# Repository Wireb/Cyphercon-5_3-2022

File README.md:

# Cyphercon 5.3 2022 
This repo is a collection of files related to the Cyphercon 5.3 badge and support hardware. 
Peacock board files and data pulled out to make the lifetime badges a bit harder to forge. 

## KiCad
This is a KiCad 5.x project. 

## MplabX
This is a mplabX 5.35 project. All programming / debug was done with a PicKit4.

## FreeCAD
These are FreeCAD 0.19 

## Inkscape
Version 1.0.1 used

## Documentation

- Cyphercon 2020.xlsx - Master document used for badge development. BOMs, communication, game mech, flash layout, animation documentation
- FreeCAD/Start button-2022  Cad files related to the conference start button
- FreeCAD/tymkrs_Cyphercon_2022 Cad files related to the badge and vending machine 
   - bottle_button_support.FCStd - support structure for IR button used in the snake oil button 
   - button_case.FCStd - support structure for IR button used in the bee and bird seed bags
   - coyote_final.FCStd - screen alignment tool
   - coyote_stencil.FCStd - flocking stencil and blocks
   - flamingo_final.FCStd - screen alignment tool
   - flamingo_flock_blocks.FCStd - alignment blocks for badge on stencil machine 
   - flamingo_pgm_fixture.FCStd - programing fixture for flamingo badges
   - flamingo_stencil_2_tone_a.FCStd - flocking stencil
   - flamingo_stencil_V2.FCStd - flocking stencil
   - llama_final.FCStd - screen alignment tool
   - llama_stencil.FCStd - flocking stencil and blocks
   - Outhouse_socket.FCStd - socket for holding badge in outhouse
   - parrot_final.FCStd - screen alignment tool
   - parrot_stencil.FCStd - flocking stencil and blocks
   - peacock_final.FCStd - screen alignment tool
   - port_a_potty.FCStd - port-a-potty IR button housing 
   - Starfish.FCStd - starfish stencil for back of all the badges
   - Vendo_bracket.FCStd - support bracket for replacement processor board in the vending machine
   - Vendo_socket.FCStd - socket for badge on front of the vending machine 
   - wash_holders.FCStd - holder for running PCBs though flux remover in the ultrasonic cleaner
- inkscape - Intermediate files used to build up the stencils from the silk screen layers
- kicad 
   - tymkrs_Cyphercon_2020_Coyote - Coyote badge files
   - tymkrs_Cyphercon_2020_flamingo - Flamingo badge files
   - tymkrs_Cyphercon_2020_IRbutton - IR button files 
   - tymkrs_Cyphercon_2020_IRhack - IR hack and start button board (note start button was highly modified and mostly just used as a PIC chip holder.)
   - tymkrs_Cyphercon_2020_Llama - Llama badge files
   - tymkrs_Cyphercon_2020_Parrot - Parrot badge files 
   - tymkrs_vendo - Vendo processor replacement board (note "vendo.???" files are my schematics from reverse engineering the vending machine board) 
- mplab
    - Tymkrs_Cyphercon2020_IRblaster - Firmware for con start button
    - Tymkrs_Cyphercon2020_IRhack - Firmware for IRhack board 
    - Tymkrs_Cyphercon_2020_badge - Firmware for badges (one build supports all. Function defined by ID range) 
    - Tymkrs_Cyphercon_2020_IRbutton - Firmware for IR buttons and outhouses (Note there is a #ifdef to set outhouse vs IR button mode) 
- perl
   - Animation_build_list - flamingo.txt - build list to go with build_animations.pl script to generate animation_flamingo.bin
   - Animation_build_list_CPL.txt - build list to go with build_animations.pl script to generate animation_CPL.bin
   - Animation_build_list_peacock.txt - build list to go with animation_peacock.pl script to generate animation_flamingo.bin
   - animation_CPL.bin - output animation data file that should be written to the SPI eeprom on the badge for coyote, parrot, and llama
   - animation_flamingo.bin - output animation data file that should be written to the SPI eeprom on the badge
   - animation_peacock.bin - output animation data file that should be written to the SPI eeprom on the badge
   - build_animations.pl - this script takes in the animation frames in PNG format per the animation_build_list and generates the binary files to be written to the - eeprom
   - CPL_eyes - file folder of png files for coyote, parrot, and llama
   - cyphercon2020-pgm.pl - programing script for the PIC generate random key for crypto and takes user input for badge ID (badge type is determined by ID range. See documentation)
   - cyphercon2022.db - database dump from the vending machine 
   - Cyphercon_2020_test.pl - test utility to be use with a IR hack to gest the various badge communication functions
   - F_eyes - file folder of png files for flamingos
   - hbdh.png - Happy birthday Hyr0n (was going to be on his birthday in 2020... Happy belated bday Hyr0n) 
   - metroid.png - PNG used in base firmware to test the LCD when the SPI eeprom is not programed
   - P_eyes - file folder of png files for peacocks
   - Tymkrs_Cyphercon_2020_badge.X.production.hex - final released firmware (should be the same as the copy in the mplab directory... I hope) 
   - Tymkrs_Cyphercon_2020_keys.txt - Master list of keys used in the vending machine. Use the last one in the file when duplicates badge IDs are found. 
   - Vending_data.xlsx - Decoded dump in excel with some post processing to get some stats
   - Vendo_decode.pl - used to export the vending machine database to CSV files
   - Vendo_server.pl - Vending machine server script that did all the vending machine functions other that the monitor display
   - Vendo_test.pl - test script for the vending machine controller board

Copyright (c) 2019 - 2022 Peter Shabino

Permission is hereby granted, free of charge, to any person obtaining a copy of this hardware, software, and associated documentation files 
(the "Product"), to deal in the Product without restriction, including without limitation the rights to use, copy, modify, merge, publish, 
distribute, sublicense, and/or sell copies of the Product, and to permit persons to whom the Product is furnished to do so, subject to the 
following conditions:

The above copyright notice and this permission notice shall be included in all copies or substantial portions of the Product.

THE PRODUCT IS PROVIDED "AS IS", WITHOUT WARRANTY OF ANY KIND, EXPRESS OR IMPLIED, INCLUDING BUT NOT LIMITED TO THE WARRANTIES OF 
MERCHANTABILITY, FITNESS FOR A PARTICULAR PURPOSE AND NONINFRINGEMENT. IN NO EVENT SHALL THE AUTHORS OR COPYRIGHT HOLDERS BE LIABLE 
FOR ANY CLAIM, DAMAGES OR OTHER LIABILITY, WHETHER IN AN ACTION OF CONTRACT, TORT OR OTHERWISE, ARISING FROM, OUT OF OR IN CONNECTION 
WITH THE PRODUCT OR THE USE OR OTHER DEALINGS IN THE PRODUCT.

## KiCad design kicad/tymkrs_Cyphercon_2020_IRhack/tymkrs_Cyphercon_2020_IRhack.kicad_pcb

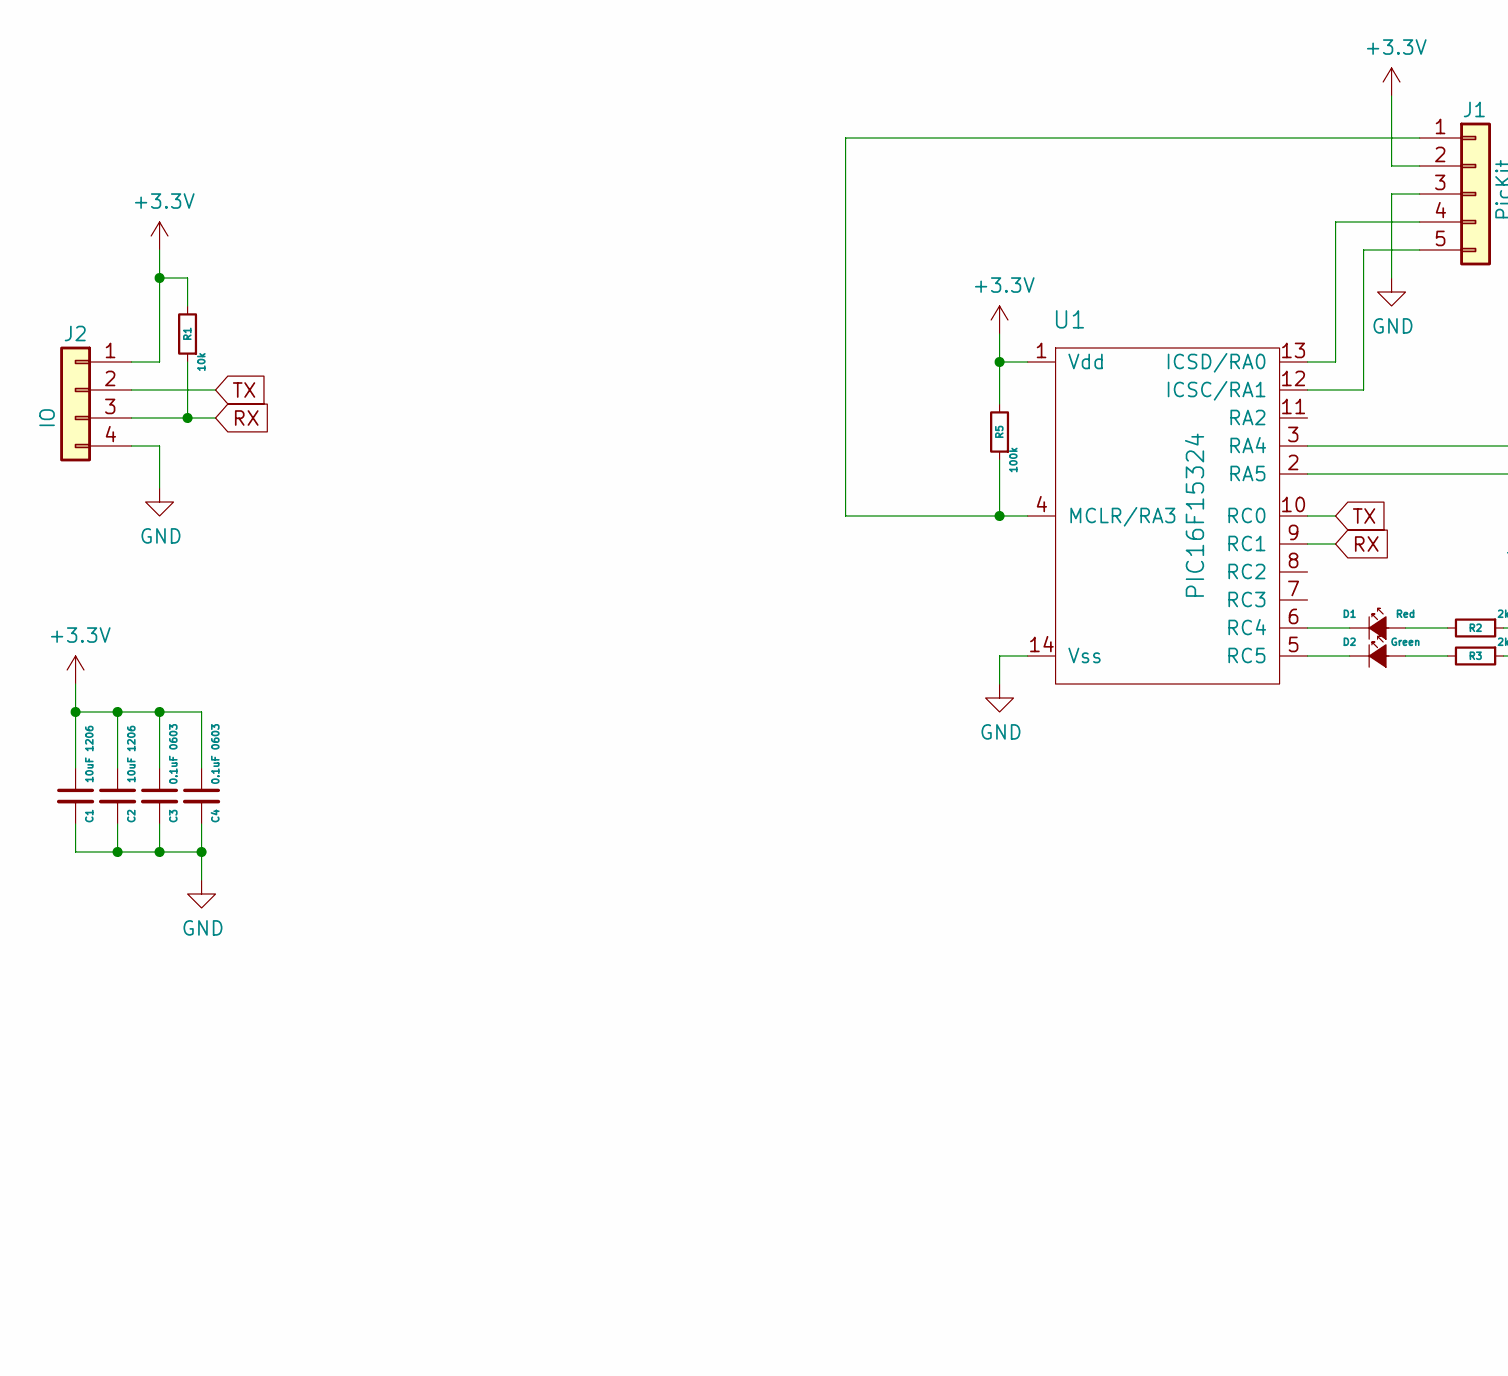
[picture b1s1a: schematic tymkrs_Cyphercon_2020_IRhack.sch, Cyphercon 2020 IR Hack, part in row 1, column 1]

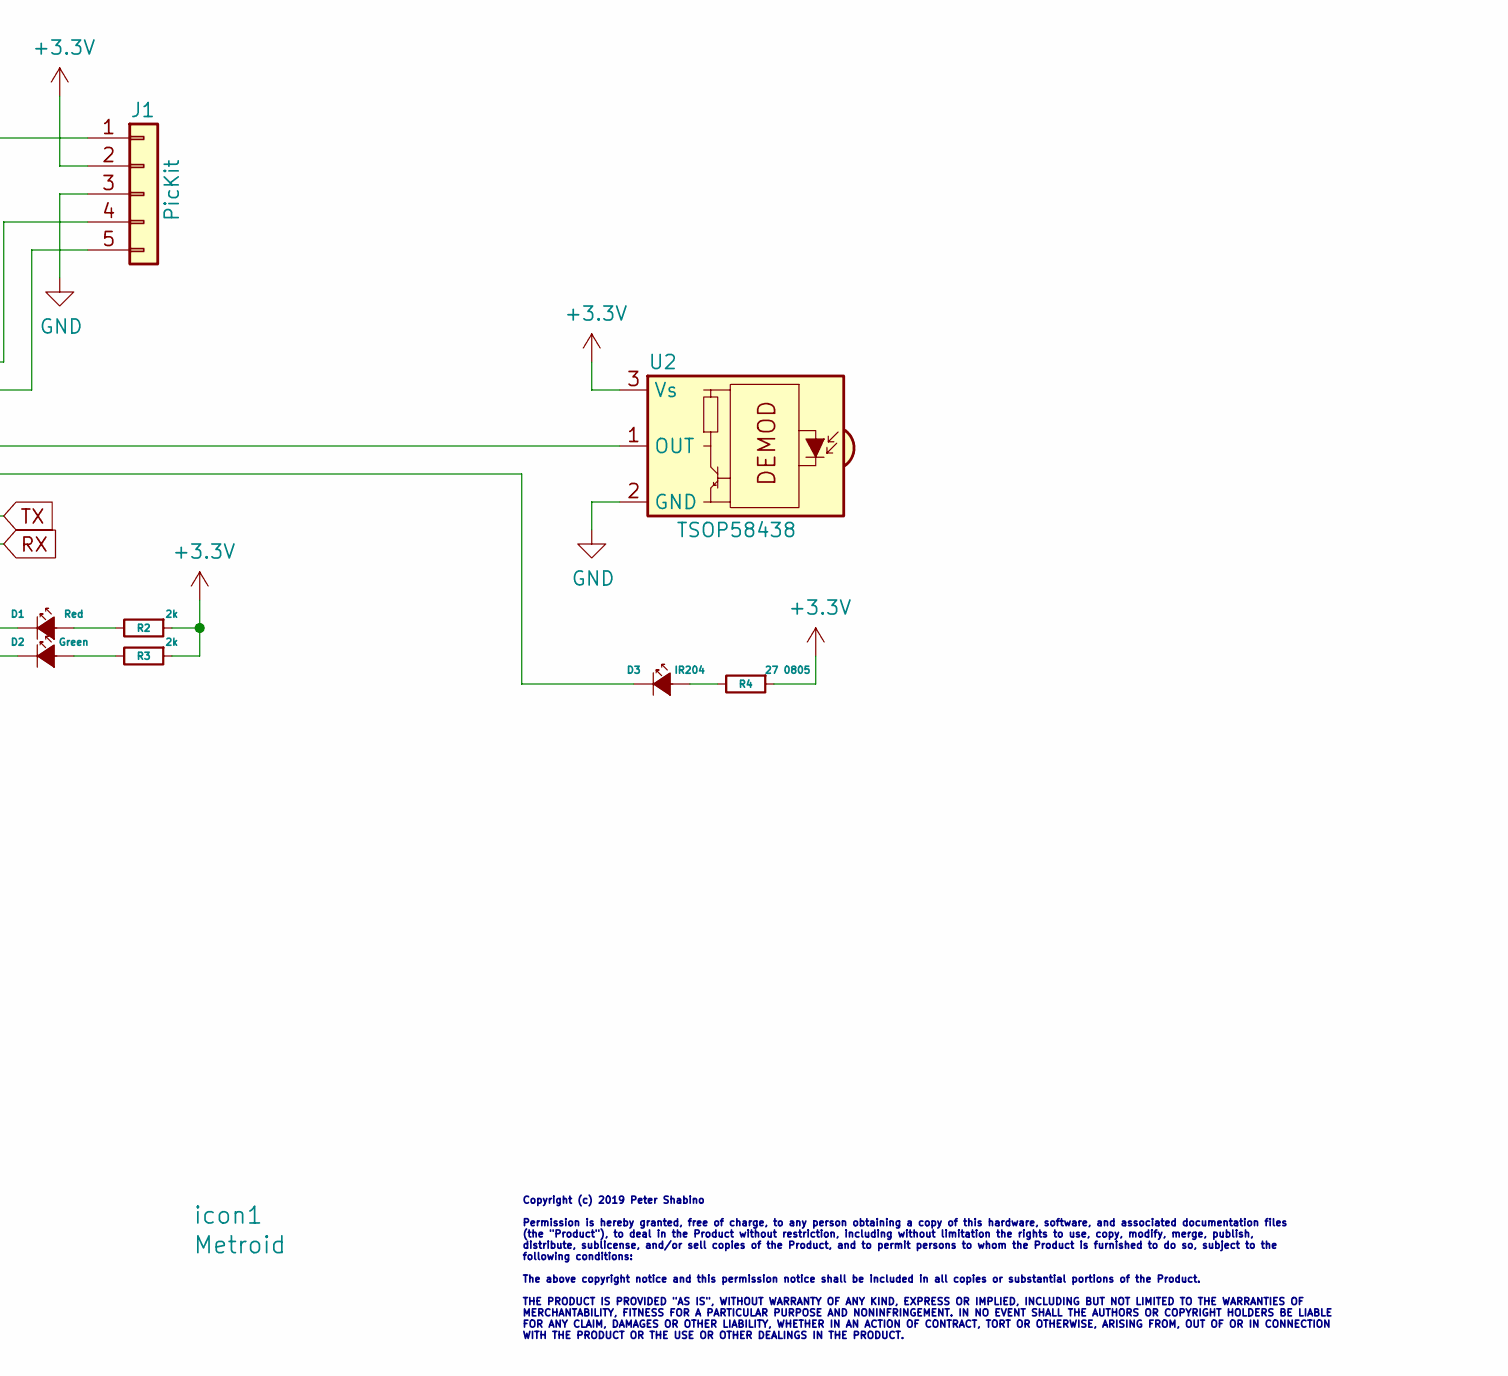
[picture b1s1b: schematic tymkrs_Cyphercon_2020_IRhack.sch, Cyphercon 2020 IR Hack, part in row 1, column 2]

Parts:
C1, C2: 10uF 1206; C_1206_3216Metric
C3, C4: 0.1uF 0603; C_0603_1608Metric
D1: Red; LED_0603_1608Metric
D2: Green; LED_0603_1608Metric
D3: IR204; LED_D3.0mm_Horizontal_O1.27mm_Z2.0mm_Clear
J1: PicKit; PinHeader_1x05_P2.54mm_Vertical
J2: IO; PinHeader_1x04_P2.54mm_Horizontal
R1: 10k; R_0603_1608Metric
R2, R3: 2k; R_0603_1608Metric
R4: 27 0805; R_0603_1608Metric
R5: 100k; R_0603_1608Metric
U1: PIC16F15324; SOIC-14_3.9x8.7mm_P1.27mm
U2: TSOP58438; TSOP48
icon1: Metroid; metroid

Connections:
+3V3: C1.1, C2.1, C3.1, C4.1, J1.2, J2.1, R1.2, R2.1, R3.1, R4.1, R5.2, U1.1 (Vdd), U2.3 (Vs)
GND: C1.2, C2.2, C3.2, C4.2, J1.3, J2.4, U1.14 (Vss), U2.2 (GND)
unnamed: D1.1 (K), U1.6 (RC4)
unnamed: D1.2 (A), R2.2
unnamed: D2.1 (K), U1.5 (RC5)
unnamed: D2.2 (A), R3.2
unnamed: D3.1 (K), U1.2 (RA5)
unnamed: D3.2 (A), R4.2
unnamed: J1.1, R5.1, U1.4 (MCLR/RA3)
unnamed: J1.4, U1.13 (ICSD/RA0)
unnamed: J1.5, U1.12 (ICSC/RA1)
unnamed: U1.3 (RA4), U2.1 (OUT)
RX: J2.3, R1.1, U1.9 (RC1)
TX: J2.2, U1.10 (RC0)

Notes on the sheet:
Copyright (c) 2019 Peter Shabino Permission is hereby granted, free of charge, to any person obtaining a copy of this hardware, software, and associated documentation files (the "Product"), to deal in the Product without restriction, including without limitation the rights to use, copy, modify, mer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

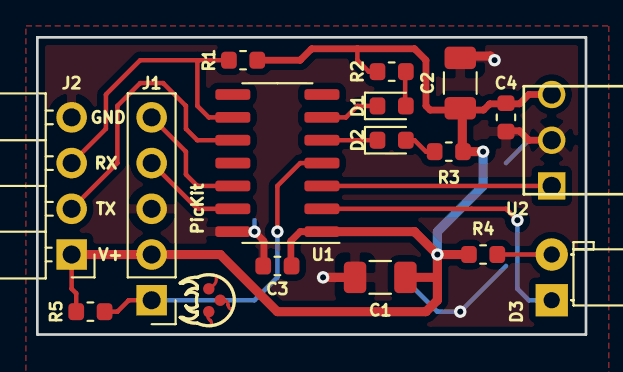
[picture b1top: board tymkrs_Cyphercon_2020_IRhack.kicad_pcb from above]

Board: 2 copper layers, 30.5 x 16.5 mm, 17 parts (0 on the bottom side), 14 nets.

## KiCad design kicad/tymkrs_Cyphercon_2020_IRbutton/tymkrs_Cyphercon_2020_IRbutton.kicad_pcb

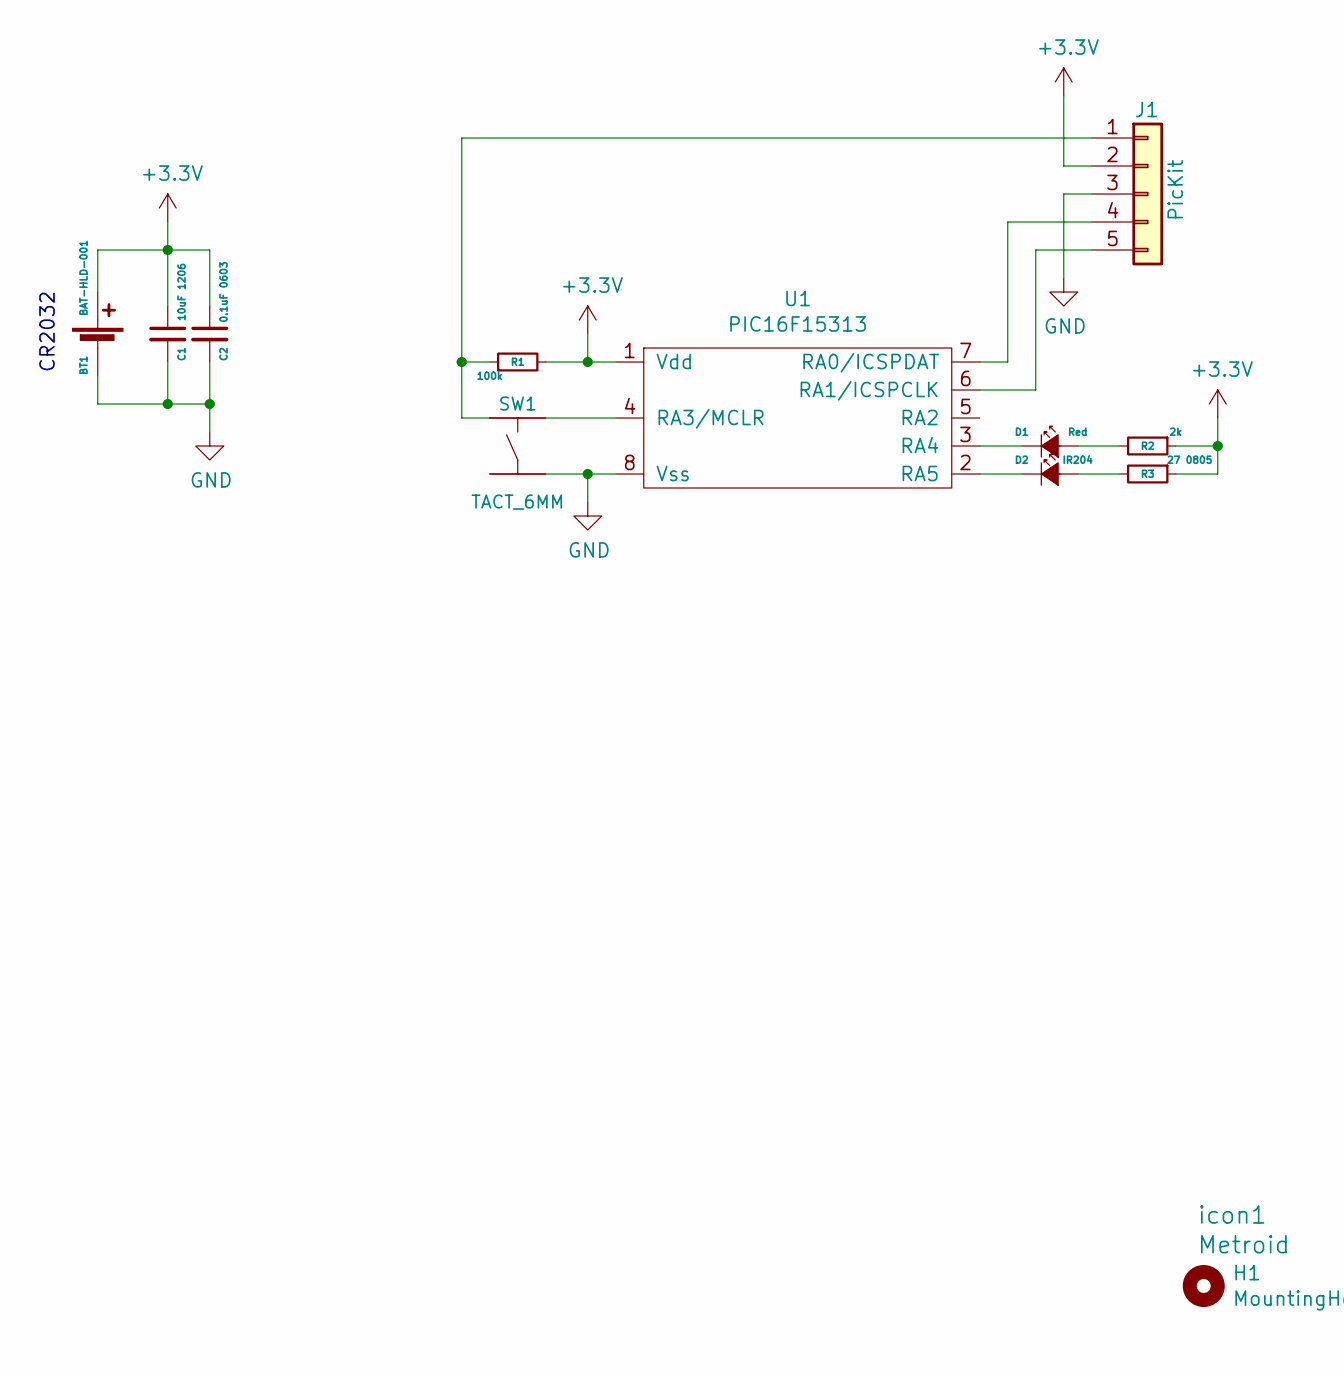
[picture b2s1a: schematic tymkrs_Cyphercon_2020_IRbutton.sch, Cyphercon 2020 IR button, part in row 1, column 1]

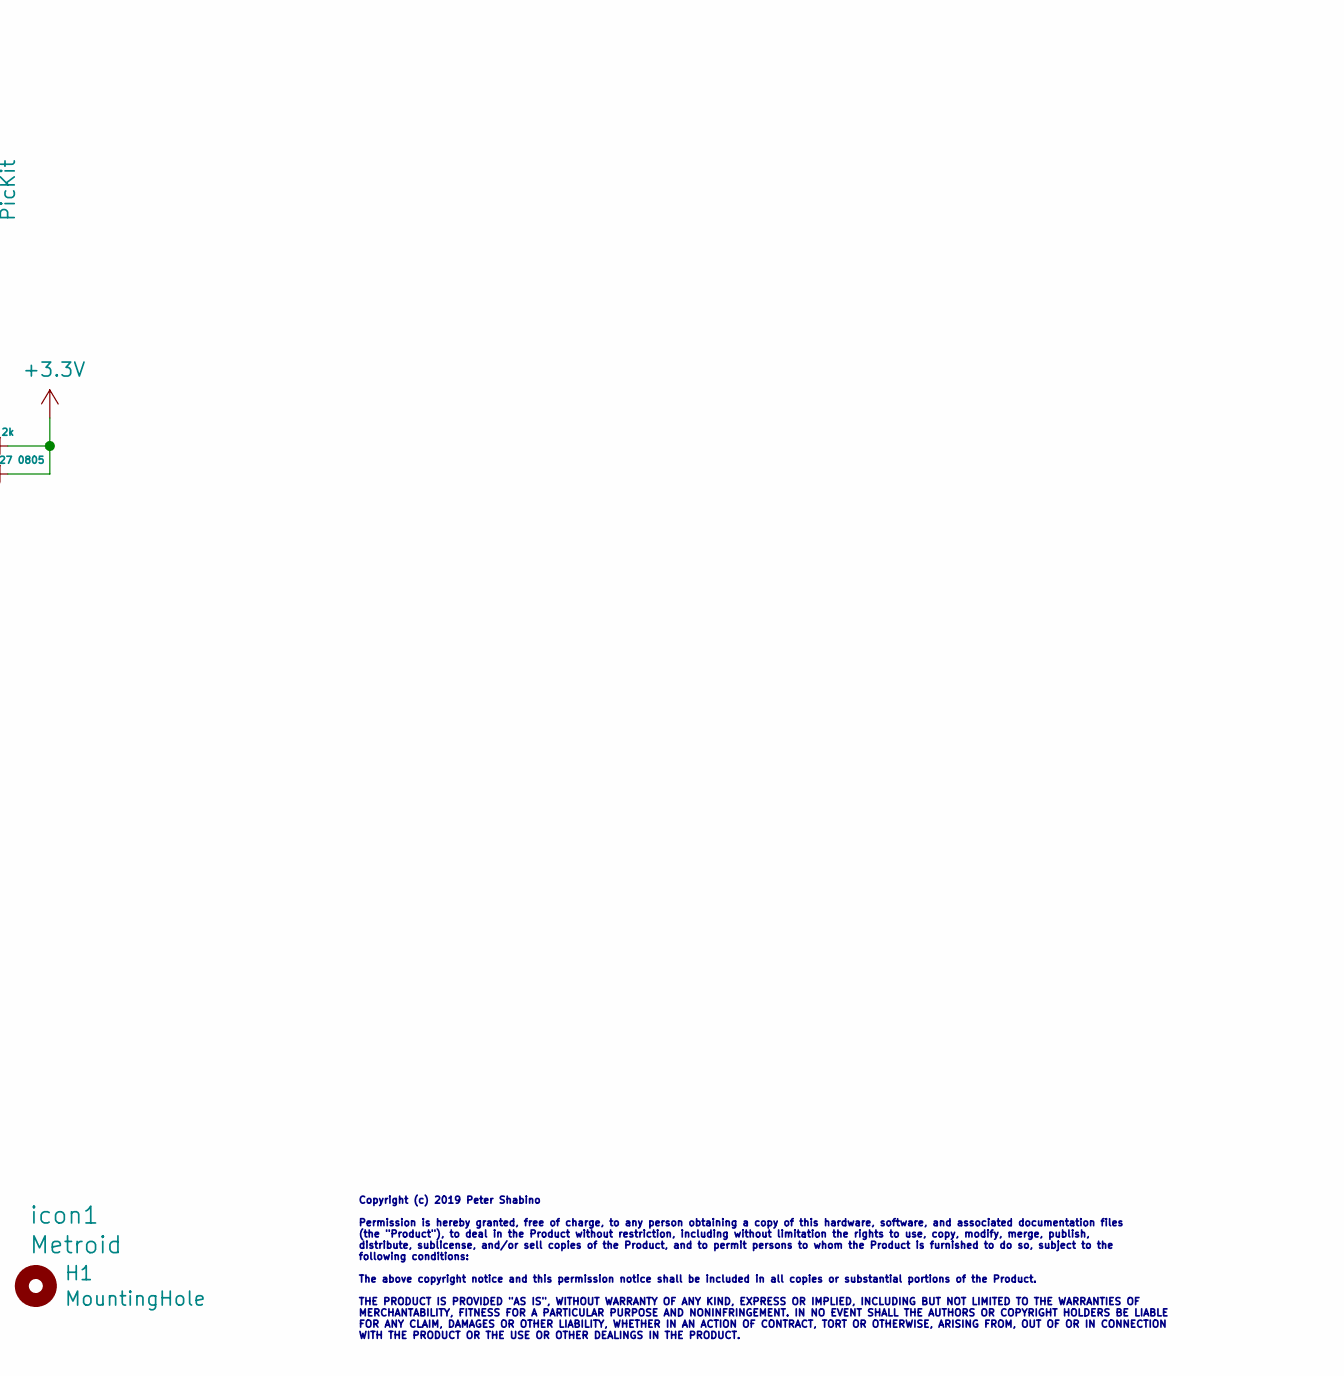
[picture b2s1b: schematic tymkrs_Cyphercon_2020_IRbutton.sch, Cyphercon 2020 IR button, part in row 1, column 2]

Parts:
BT1: BAT-HLD-001
C1: 10uF 1206; C_1206_3216Metric
C2: 0.1uF 0603; C_0603_1608Metric
D1: Red; LED_0603_1608Metric
D2: IR204; LED_D3.0mm_Horizontal_O1.27mm_Z2.0mm_Clear
H1: MountingHole; MountingHole_2.7mm_M2.5
J1: PicKit; PinHeader_1x05_P2.54mm_Vertical
R1: 100k; R_0603_1608Metric
R2: 2k; R_0603_1608Metric
R3: 27 0805; R_0603_1608Metric
SW1: TACT_6MM; PTS645_6mm_tact_sw
U1: PIC16F15313; SOIC-8_3.9x4.9mm_P1.27mm
icon1: Metroid; metroid

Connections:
+3V3: BT1.1 (+), C1.1, C2.1, J1.2, R1.2, R2.1, R3.1, U1.1 (Vdd)
GND: BT1.2 (-), C1.2, C2.2, J1.3, SW1.4, U1.8 (Vss)
unnamed: D1.1 (K), U1.3 (RA4)
unnamed: D1.2 (A), R2.2
unnamed: D2.1 (K), U1.2 (RA5)
unnamed: D2.2 (A), R3.2
unnamed: J1.1, R1.1, SW1.1
unnamed: J1.4, U1.7 (RA0/ICSPDAT)
unnamed: J1.5, U1.6 (RA1/ICSPCLK)
unnamed: SW1.2, U1.4 (RA3/MCLR)

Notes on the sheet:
Copyright (c) 2019 Peter Shabino Permission is hereby granted, free of charge, to any person obtaining a copy of this hardware, software, and associated documentation files (the "Product"), to deal in the Product without restriction, including without limitation the rights to use, copy, modify, mer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
CR2032

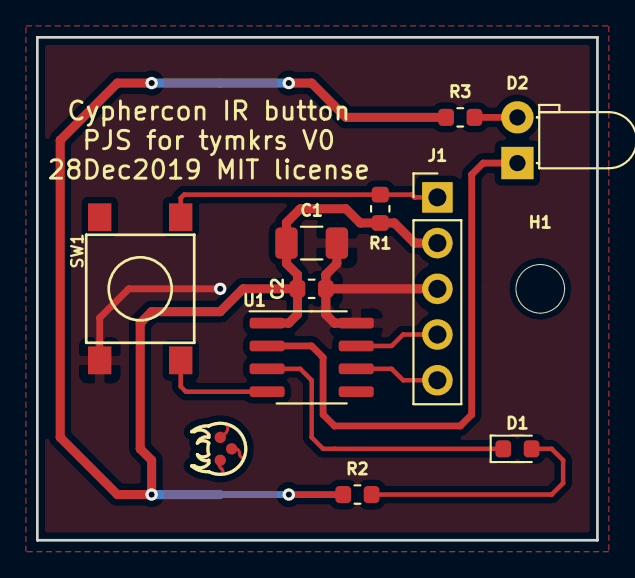
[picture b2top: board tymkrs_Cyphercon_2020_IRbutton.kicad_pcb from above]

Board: 2 copper layers, 31.1 x 27.9 mm, 13 parts (1 on the bottom side), 10 nets.

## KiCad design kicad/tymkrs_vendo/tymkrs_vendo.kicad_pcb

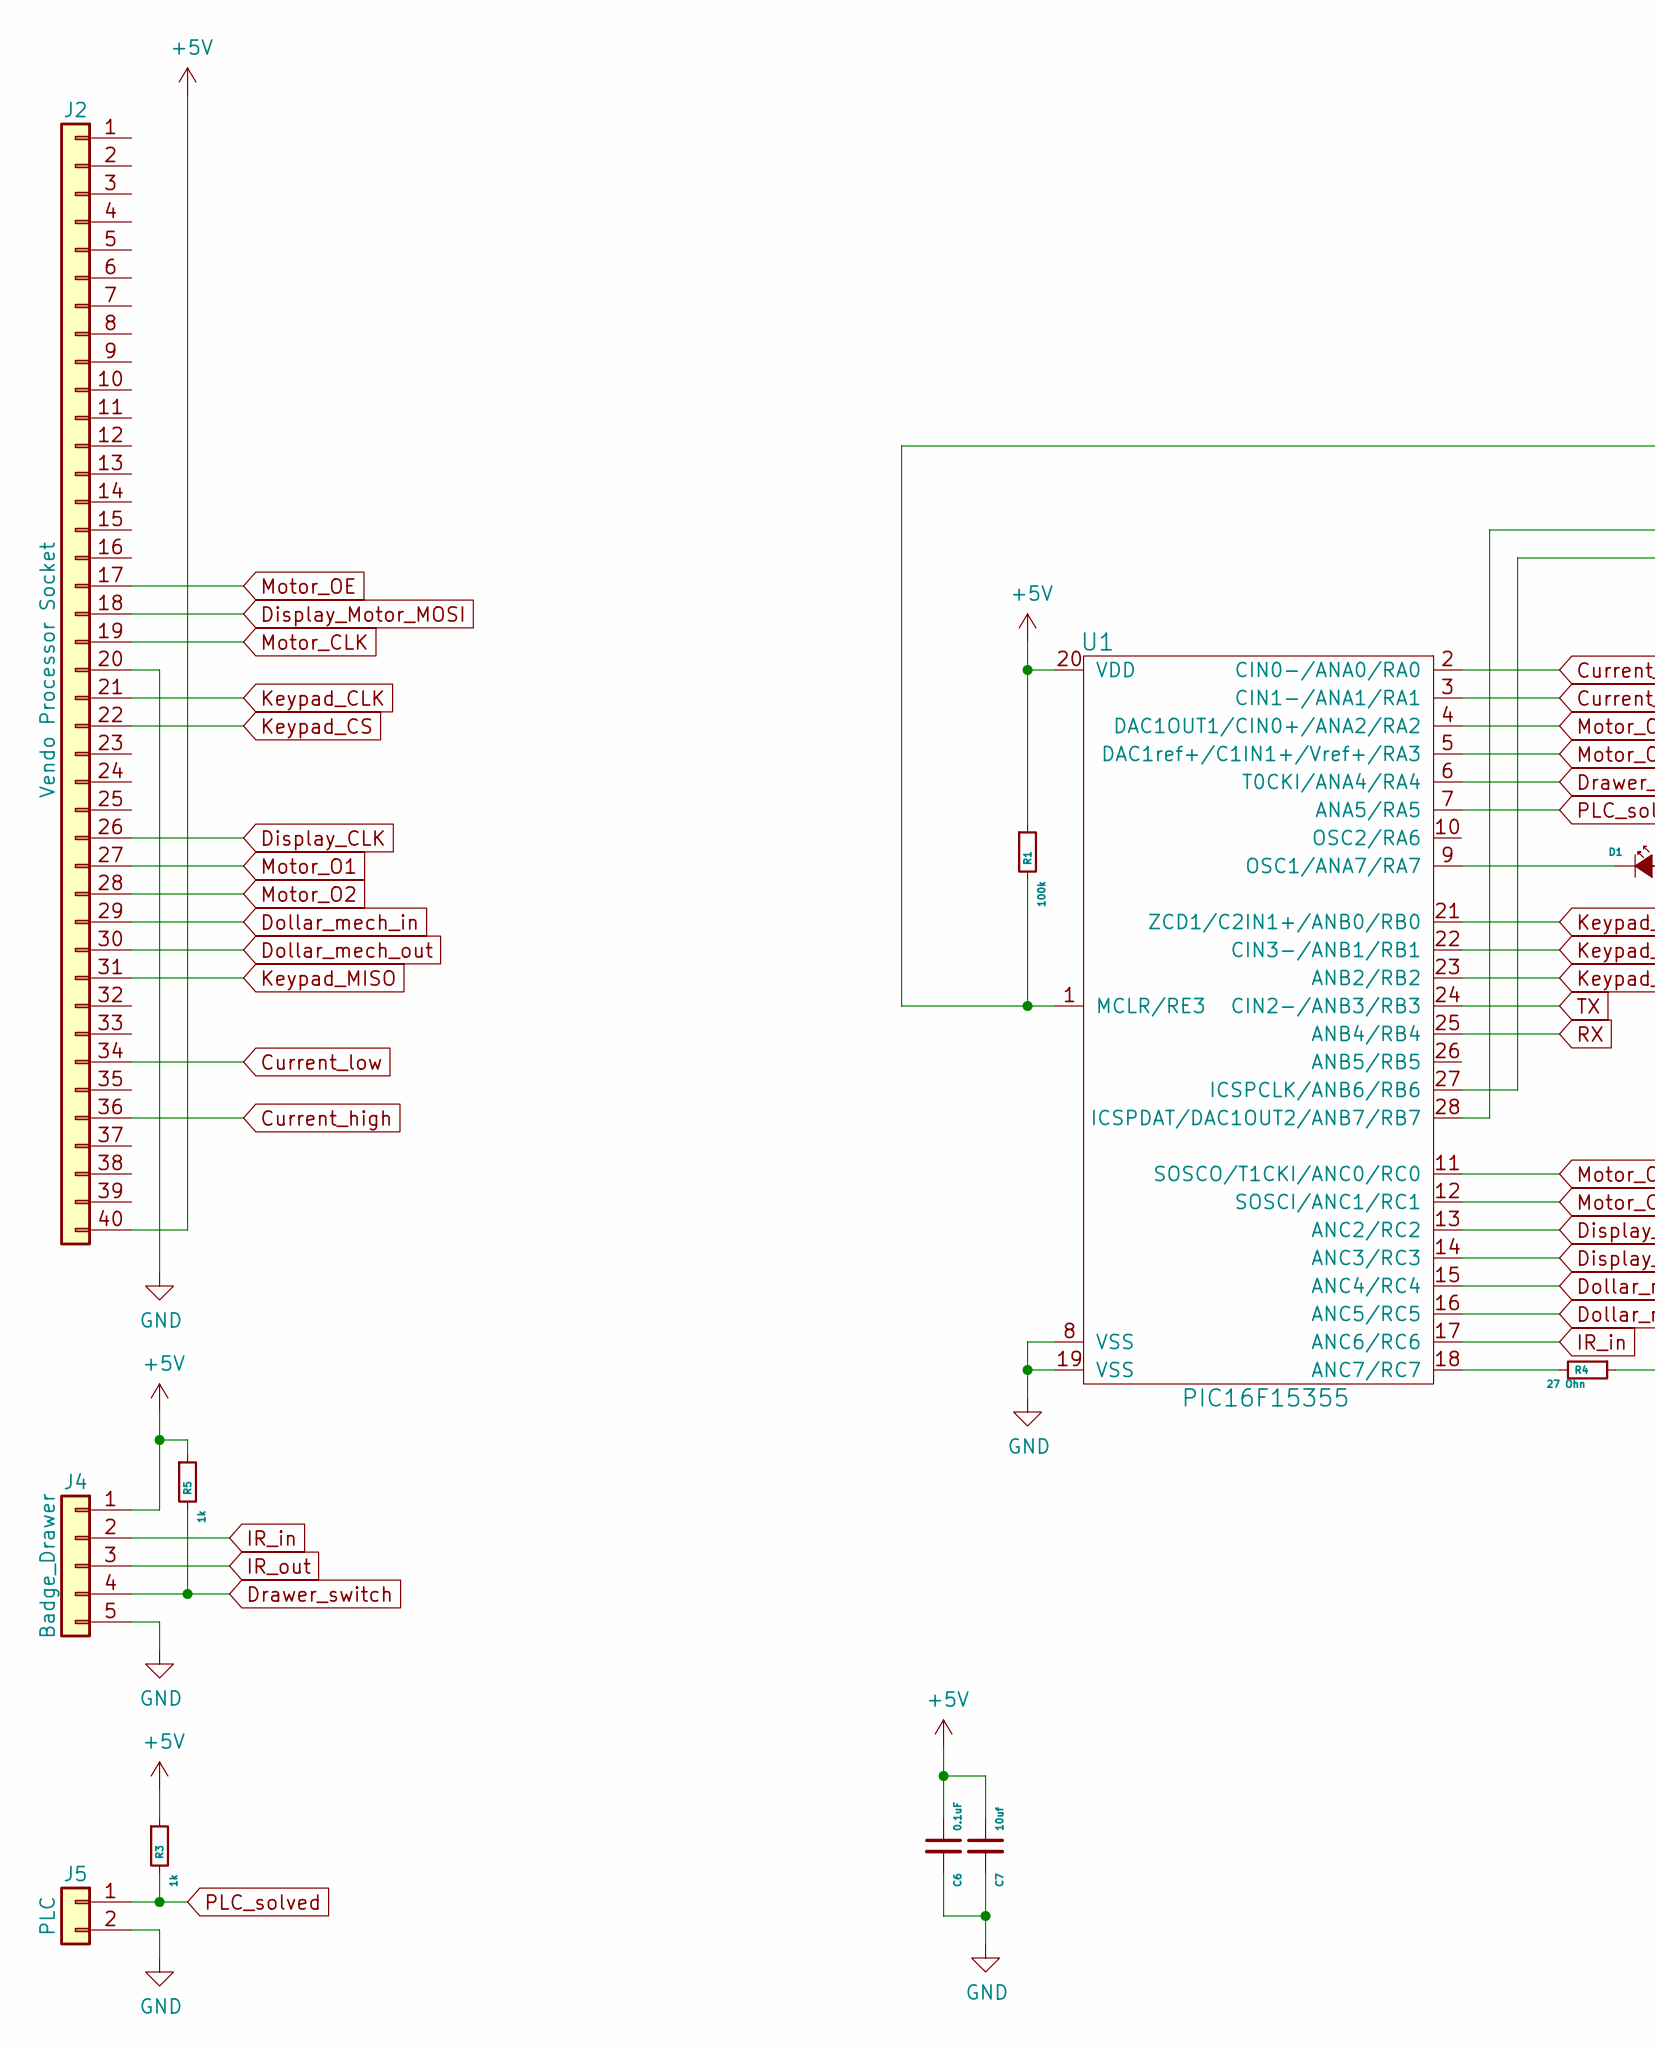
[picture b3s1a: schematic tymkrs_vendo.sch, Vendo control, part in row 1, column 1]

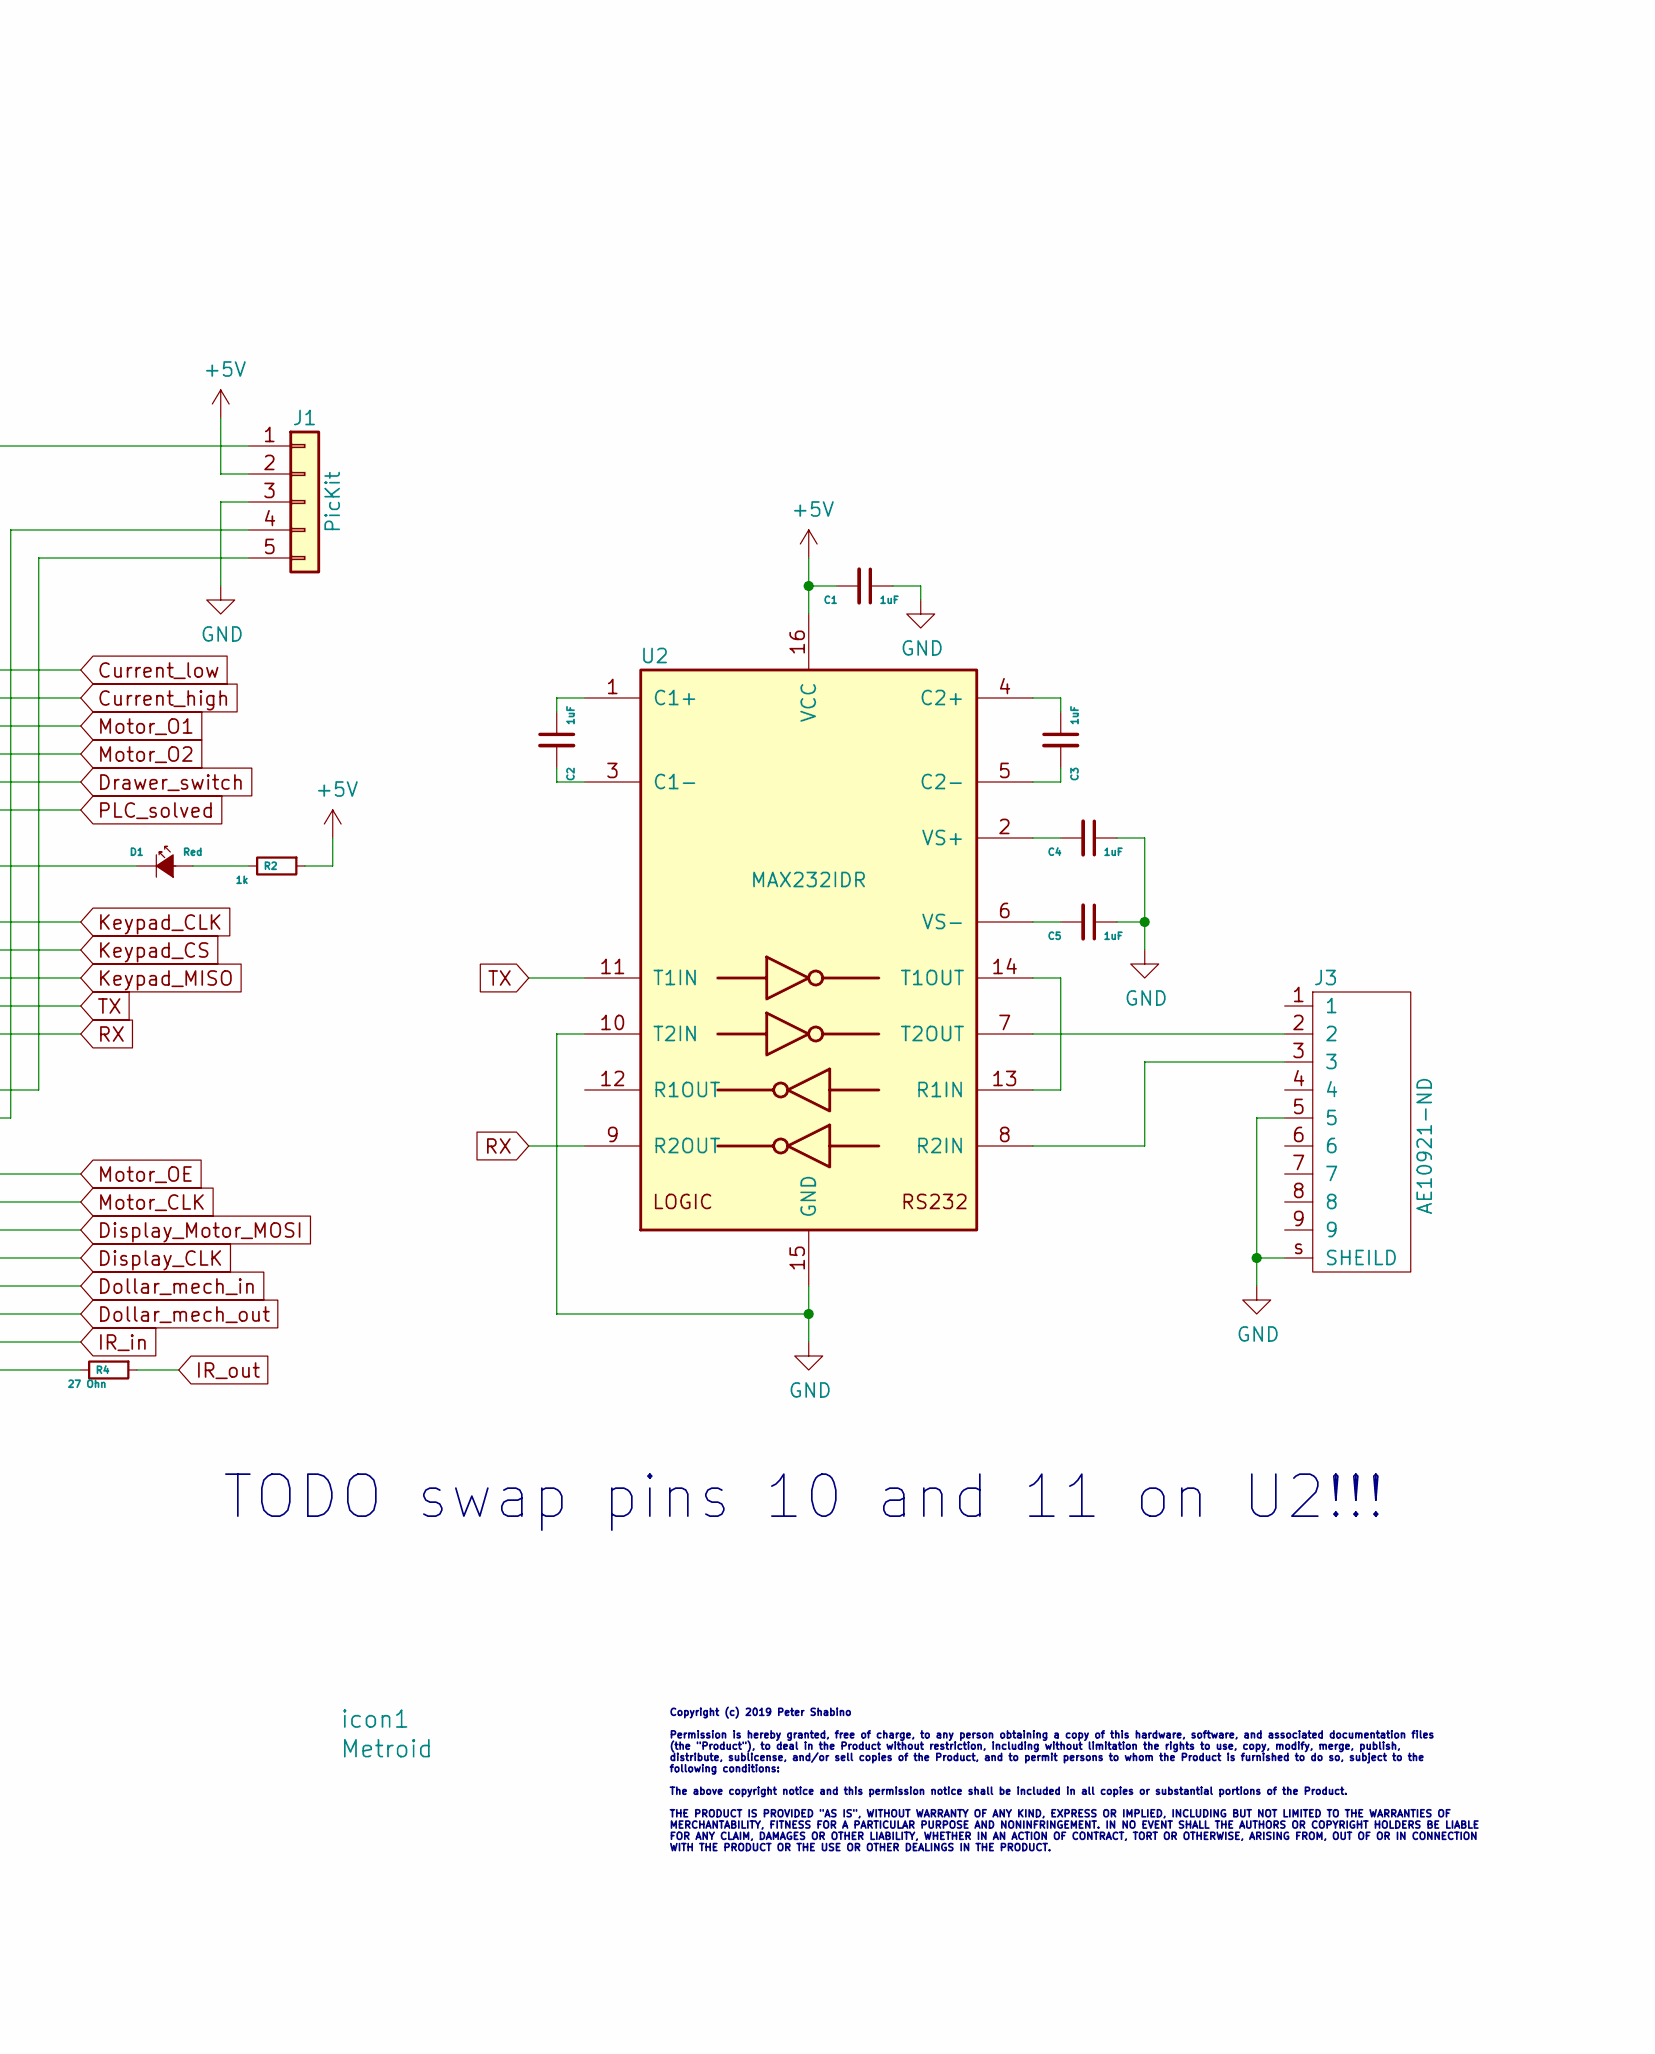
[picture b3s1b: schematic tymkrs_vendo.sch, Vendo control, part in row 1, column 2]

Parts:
C1, C2, C3, C4, C5: 1uF; C_0805_2012Metric
C6: 0.1uF; C_0603_1608Metric
C7: 10uf; C_1206_3216Metric
D1: Red; LED_0603_1608Metric
J1: PicKit; PinHeader_1x05_P2.54mm_Vertical
J2: Vendo Processor Socket; DIP-40_W15.24mm_Socket_LongPads
J3: AE10921-ND; ASSMANN_dsub-9F_RA_AE10921-ND
J4: Badge_Drawer; PinHeader_1x05_P2.54mm_Vertical
J5: PLC; PinHeader_1x02_P2.54mm_Vertical
R1: 100k; R_0603_1608Metric
R2, R3, R5: 1k; R_0603_1608Metric
R4: 27 Ohn; R_0805_2012Metric
U1: PIC16F15355; SOIC-28W_7.5x18.7mm_P1.27mm
U2: MAX232IDR; SOIC-16_3.9x9.9mm_P1.27mm
icon1: Metroid; metroid

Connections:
+5V: C1.2, C6.1, C7.1, J1.2, J2.40, J4.1, R1.1, R2.1, R3.1, R5.1, U1.20 (VDD), U2.16 (VCC)
Current_high: J2.36, U1.3 (CIN1-/ANA1/RA1)
Current_low: J2.34, U1.2 (CIN0-/ANA0/RA0)
Display_CLK: J2.26, U1.14 (ANC3/RC3)
Display_Motor_MOSI: J2.18, U1.13 (ANC2/RC2)
Dollar_mech_in: J2.29, U1.15 (ANC4/RC4)
Dollar_mech_out: J2.30, U1.16 (ANC5/RC5)
Drawer_switch: J4.4, R5.2, U1.6 (T0CKI/ANA4/RA4)
GND: C1.1, C4.1, C5.1, C6.2, C7.2, J1.3, J2.20, J3.5, J3.s (SHEILD), J4.5, J5.2, U1.8 (VSS), U1.19 (VSS), U2.10 (T2IN), U2.15 (GND)
IR_in: J4.2, U1.17 (ANC6/RC6)
IR_out: J4.3, R4.1
Keypad_CLK: J2.21, U1.21 (ZCD1/C2IN1+/ANB0/RB0)
Keypad_CS: J2.22, U1.22 (CIN3-/ANB1/RB1)
Keypad_MISO: J2.31, U1.23 (ANB2/RB2)
Motor_CLK: J2.19, U1.12 (SOSCI/ANC1/RC1)
Motor_O1: J2.27, U1.4 (DAC1OUT1/CIN0+/ANA2/RA2)
Motor_O2: J2.28, U1.5 (DAC1ref+/C1IN1+/Vref+/RA3)
Motor_OE: J2.17, U1.11 (SOSCO/T1CKI/ANC0/RC0)
unnamed: C2.1, U2.1 (C1+)
unnamed: C2.2, U2.3 (C1-)
unnamed: C3.1, U2.4 (C2+)
unnamed: C3.2, U2.5 (C2-)
unnamed: C4.2, U2.2 (VS+)
unnamed: C5.2, U2.6 (VS-)
unnamed: D1.1 (K), U1.9 (OSC1/ANA7/RA7)
unnamed: D1.2 (A), R2.2
unnamed: J1.1, R1.2, U1.1 (MCLR/RE3)
unnamed: J1.4, U1.28 (ICSPDAT/DAC1OUT2/ANB7/RB7)
unnamed: J1.5, U1.27 (ICSPCLK/ANB6/RB6)
unnamed: J3.2, U2.7 (T2OUT)
unnamed: J3.3, U2.8 (R2IN)
unnamed: R4.2, U1.18 (ANC7/RC7)
unnamed: U2.13 (R1IN), U2.14 (T1OUT)
PLC_solved: J5.1, R3.2, U1.7 (ANA5/RA5)
RX: U1.25 (ANB4/RB4), U2.9 (R2OUT)
TX: U1.24 (CIN2-/ANB3/RB3), U2.11 (T1IN)

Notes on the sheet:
Copyright (c) 2019 Peter Shabino Permission is hereby granted, free of charge, to any person obtaining a copy of this hardware, software, and associated documentation files (the "Product"), to deal in the Product without restriction, including without limitation the rights to use, copy, modify, mer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
TODO swap pins 10 and 11 on U2!!!

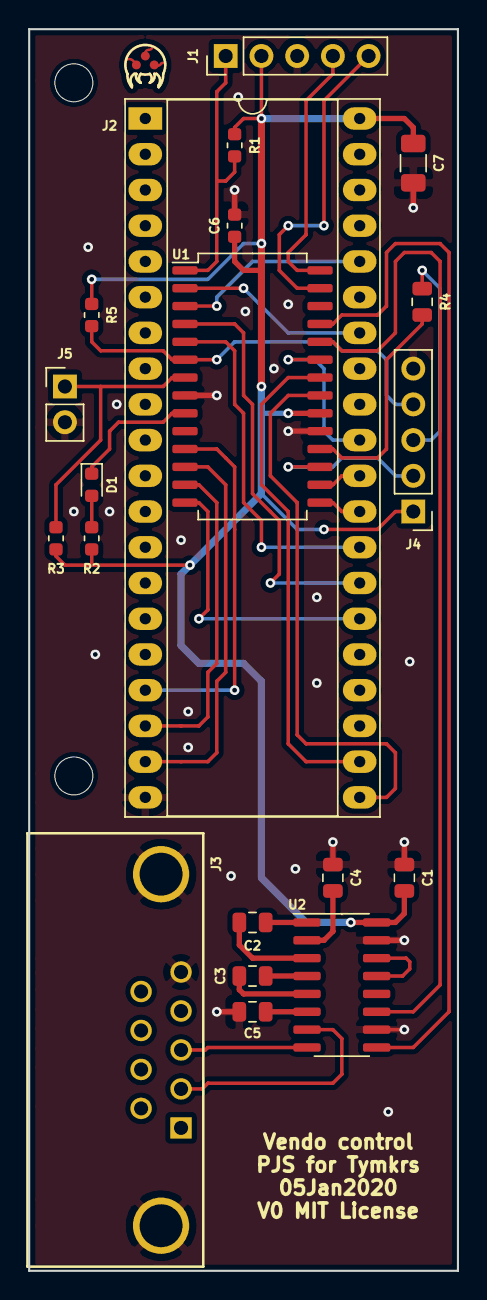
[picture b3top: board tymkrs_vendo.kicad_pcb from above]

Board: 2 copper layers, 30.5 x 88.3 mm, 21 parts (0 on the bottom side), 36 nets.

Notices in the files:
kicad/tymkrs_Cyphercon_2020_IRbutton/tymkrs_Cyphercon_2020_IRbutton.kicad_pcb:
28Dec2019 MIT license
kicad/tymkrs_Cyphercon_2020_flamingo/tymkrs_Cyphercon_2020_flamingo.kicad_pcb:
Copyright (c) 2020 Peter Shabino
04Feb2020 MIT License
kicad/tymkrs_vendo/tymkrs_vendo.kicad_pcb:
V0 MIT License
